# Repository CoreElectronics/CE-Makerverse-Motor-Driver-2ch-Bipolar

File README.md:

# Makerverse™ Motor Driver - 2 channel / BiPolar Stepper

This is the repo for the Core Electronics [Makerverse™ Motor Driver 2ch](https://core-electronics.com.au/catalog/product/view/sku/CE08038).

## License
This project is open source - please review the LICENSE.md file for further licensing information.

If you have any technical questions, or concerns about licensing, please contact technical support on the [Core Electronics forums](https://forum.core-electronics.com.au/).

*\"Makerverse\" and the Makerverse logo are trademarks of Core Electronics Pty Ltd.*

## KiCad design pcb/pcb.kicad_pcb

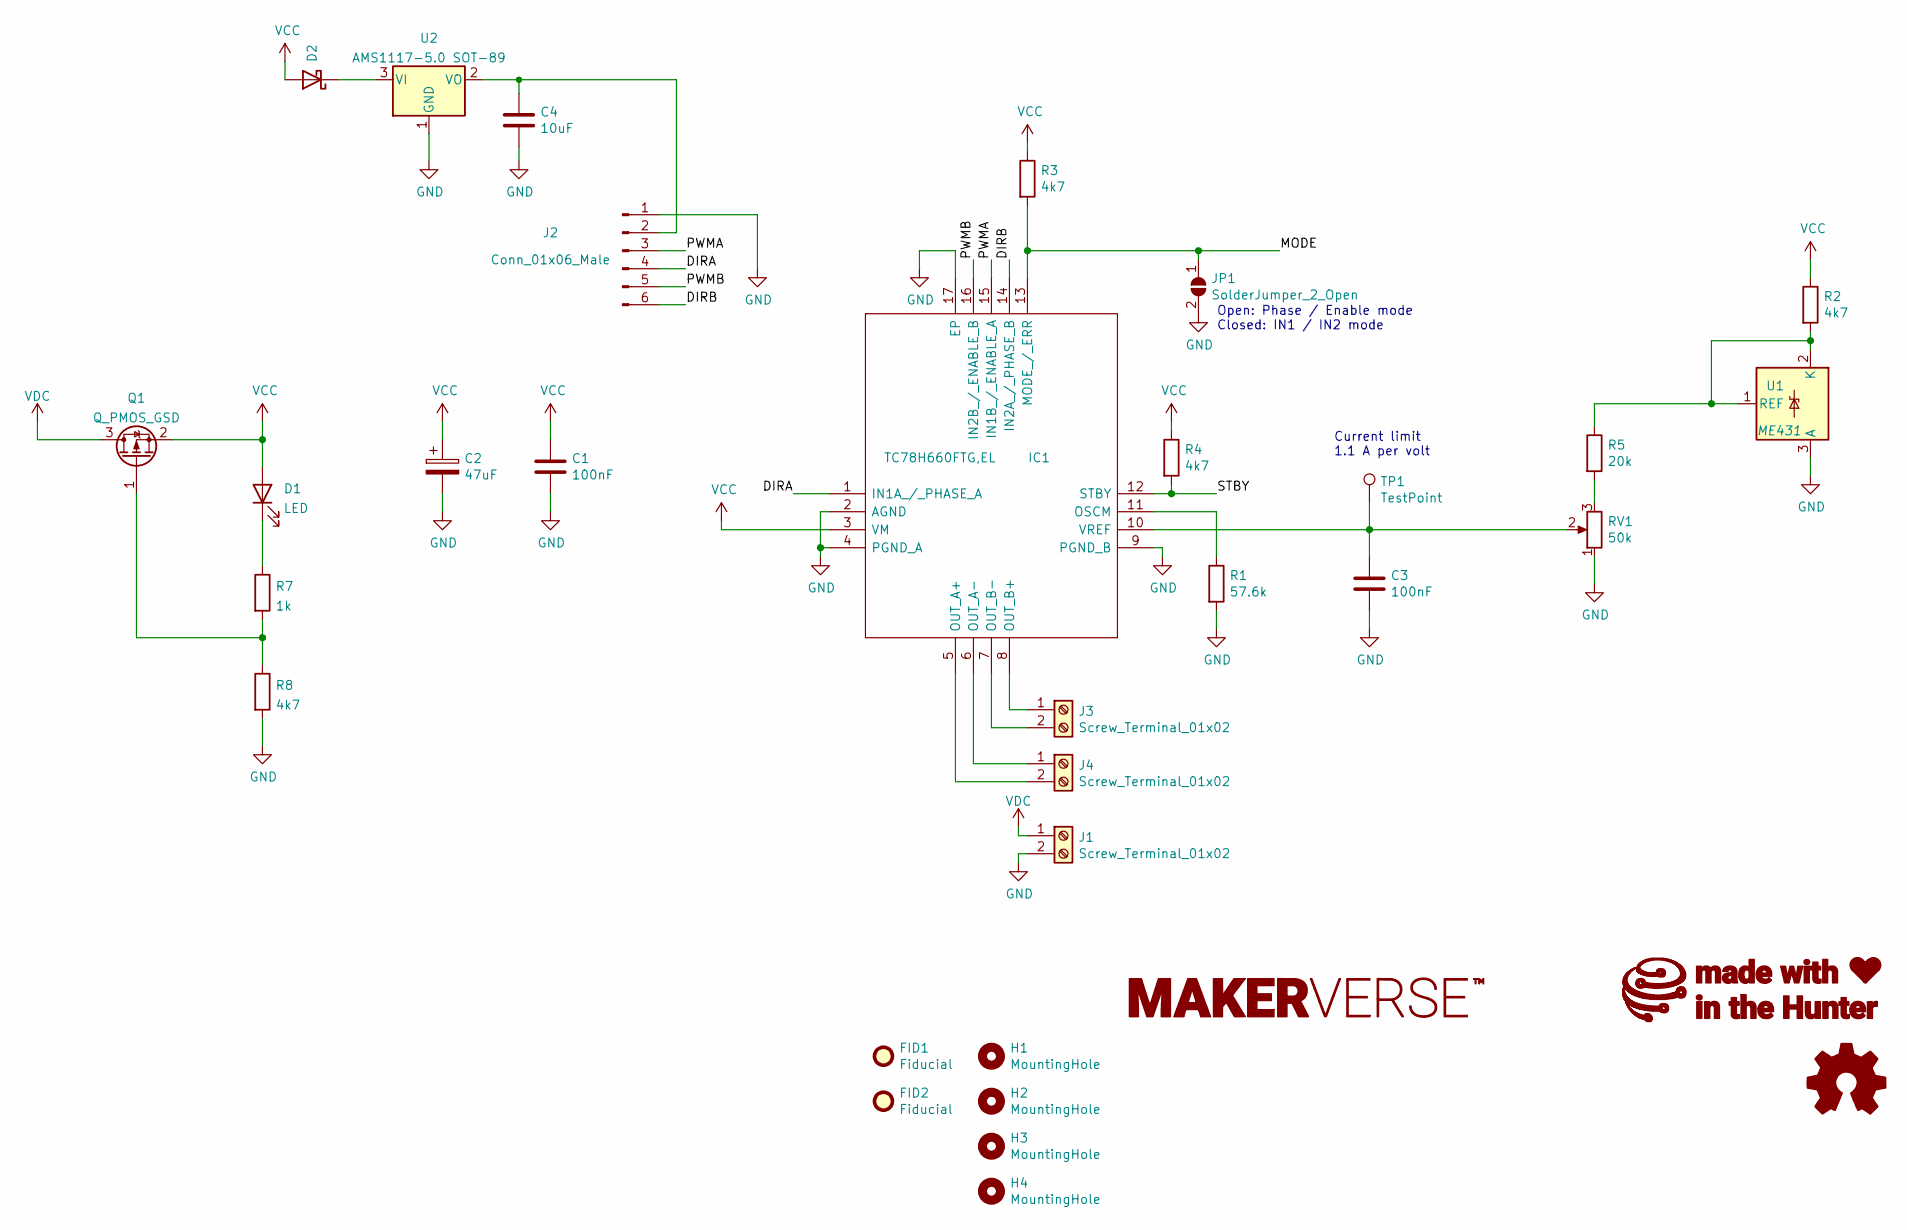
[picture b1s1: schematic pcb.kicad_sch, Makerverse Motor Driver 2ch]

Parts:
C1, C3: 100nF; C_0402_1005Metric
C2: 47uF; CP_Elec_6.3x5.3
C4: 10uF; C_0603_1608Metric
D1: LED; LED_0603_1608Metric
D2: D_Schottky; D_SMA
FID1, FID2: Fiducial; Fiducial_1mm_Mask2mm
H1, H2, H3, H4: MountingHole; MountingHole_3.2mm_M3
IC1: TC78H660FTG,EL; QFN-16-1EP_3x3mm_P0.5mm_EP1.7x1.7mm_ThermalVias; Mouser Part Number 757-TC78H660FTGEL
J1, J3, J4: Screw_Terminal_01x02; terminal-2-pin-5mm
J2: Conn_01x06_Male; PinHeader_1x06_P2.54mm_Vertical
JP1: SolderJumper_2_Open; SolderJumper-2_P1.3mm_Open_RoundedPad1.0x1.5mm_NoMask
Q1: Q_PMOS_GSD; SOT-23
R1: 57.6k; R_0402_1005Metric
R2, R3, R4, R8: 4k7; R_0402_1005Metric
R5: 20k; R_0402_1005Metric
R7: 1k; R_0402_1005Metric
RV1: 50k; smdPot
TP1: TestPoint; TestPoint_THTPad_1.5x1.5mm_Drill0.7mm
U1: ME431; SOT-23
U2: AMS1117-5.0 SOT-89; SOT-89-3

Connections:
/DIRA: IC1.1 (IN1A_/_PHASE_A), J2.4
/DIRB: IC1.14 (IN2A_/_PHASE_B), J2.6
/MODE: IC1.13 (MODE_/_ERR), JP1.1 (A), R3.2
/PWMA: IC1.15 (IN1B_/_ENABLE_A), J2.3
/PWMB: IC1.16 (IN2B_/_ENABLE_B), J2.5
/STBY: IC1.12 (STBY), R4.2
GND: C1.2, C2.2, C3.2, C4.2, IC1.2 (AGND), IC1.4 (PGND_A), IC1.9 (PGND_B), IC1.17 (EP), J1.2, J2.1, JP1.2 (B), R1.2, R8.2, RV1.1, U1.3 (A), U2.1 (GND)
unnamed: C3.1, IC1.10 (VREF), RV1.2, TP1.1
unnamed: C4.1, J2.2, U2.2 (VO)
unnamed: D1.1 (K), R7.1
unnamed: D2.1 (K), U2.3 (VI)
unnamed: IC1.5 (OUT_A+), J4.2
unnamed: IC1.6 (OUT_A-), J4.1
unnamed: IC1.7 (OUT_B-), J3.2
unnamed: IC1.8 (OUT_B+), J3.1
unnamed: IC1.11 (OSCM), R1.1
unnamed: Q1.1 (G), R7.2, R8.1
unnamed: R2.2, R5.1, U1.1 (REF), U1.2 (K)
unnamed: R5.2, RV1.3
VCC: C1.1, C2.1, D1.2 (A), D2.2 (A), IC1.3 (VM), Q1.2 (S), R2.1, R3.1, R4.1
VDC: J1.1, Q1.3 (D)

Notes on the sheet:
Current limit 1.1 A per volt
Open: Phase / Enable mode Closed: IN1 / IN2 mode

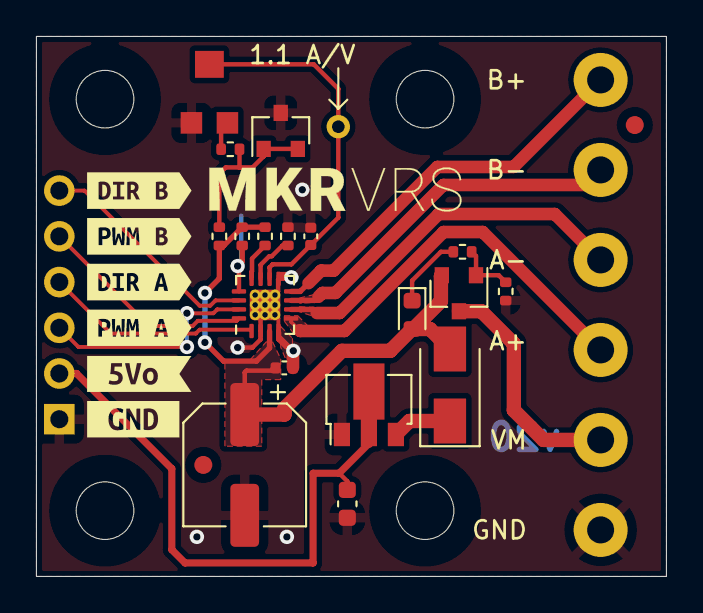
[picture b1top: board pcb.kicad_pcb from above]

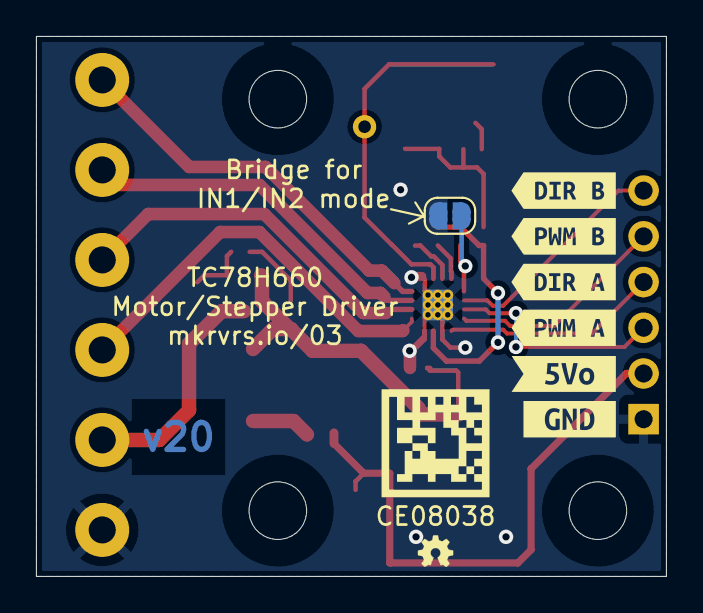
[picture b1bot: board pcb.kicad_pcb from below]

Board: 2 copper layers, 35.0 x 30.0 mm, 42 parts (7 on the bottom side), 21 nets.

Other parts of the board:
kibuzzard-62F06A1B, kibuzzard-62F06A1B#2: G***; kibuzzard-62F06A1B
kibuzzard-62F08A4D: G***; kibuzzard-62F08A4D
kibuzzard-62F08A45: G***; kibuzzard-62F08A45
kibuzzard-611F03C6, kibuzzard-611F03CE, kibuzzard-611F10A0, kibuzzard-611F10AC, kibuzzard-611F029E, kibuzzard-611F033D, kibuzzard-611F1086, kibuzzard-611F1098: G***; label

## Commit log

2022-11-07 add datasheet
2023-01-09 v20 update with voltage regulator

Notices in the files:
pcb/pcb.kicad_pcb:
License: CCASAv4.0 https://creativecommons.org/licenses/by-sa/4.0
